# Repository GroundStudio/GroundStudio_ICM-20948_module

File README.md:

GroundStudio ICM-20948 module
====================================

Get it from [ardushop.ro](https://ardushop.ro/ro/home/2659-groundstudio-icm-20948.html)

Explore all the GroundStudio products at [GroundStudio.ro](https://groundstudio.ro/)

Description
-------------------
Low power, 9-axis MotionTracking module based on ICM-20948 chip.

Contents
-------------------

* [/Documentation](https://github.com/GroundStudio/GroundStudio_ICM-20948_module/tree/main/Documentation) -- Contains documentation written during creation of this repository, with readme.md index of its own!
* [/Firmware](https://github.com/GroundStudio/GroundStudio_ICM-20948_module/tree/main/Firmware) -- Firmware (bootloaders, etc)
* [/Hardware](https://github.com/GroundStudio/GroundStudio_ICM-20948_module/tree/main/Hardware) -- Schematics, layout.
* [/Libraries](https://github.com/GroundStudio/GroundStudio_ICM-20948_module/tree/main/Libraries) -- Arduino/CircuitPython libraries. 
* [/Tools](https://github.com/GroundStudio/GroundStudio_ICM-20948_module/tree/main) -- Tools needed for compiling, uploading bootloader, etc.

Versions
-------------------
*(Not all tags shown)*
* [V0.0.1] Initial version

License
-------------------

This is released under the [Attribution-ShareAlike 4.0 International (CC BY-SA 4.0)](https://creativecommons.org/licenses/by-sa/4.0/) license. 
**You are welcome to use this for commercial purposes.**

Please consider contributing back to this project or others to help the open-source hardware community continue to thrive and grow! 

Certifications:

[Open Source Hardware Association](https://certification.oshwa.org/ro000015.html)   
   
[
](https://certification.oshwa.org/ro000015.html)

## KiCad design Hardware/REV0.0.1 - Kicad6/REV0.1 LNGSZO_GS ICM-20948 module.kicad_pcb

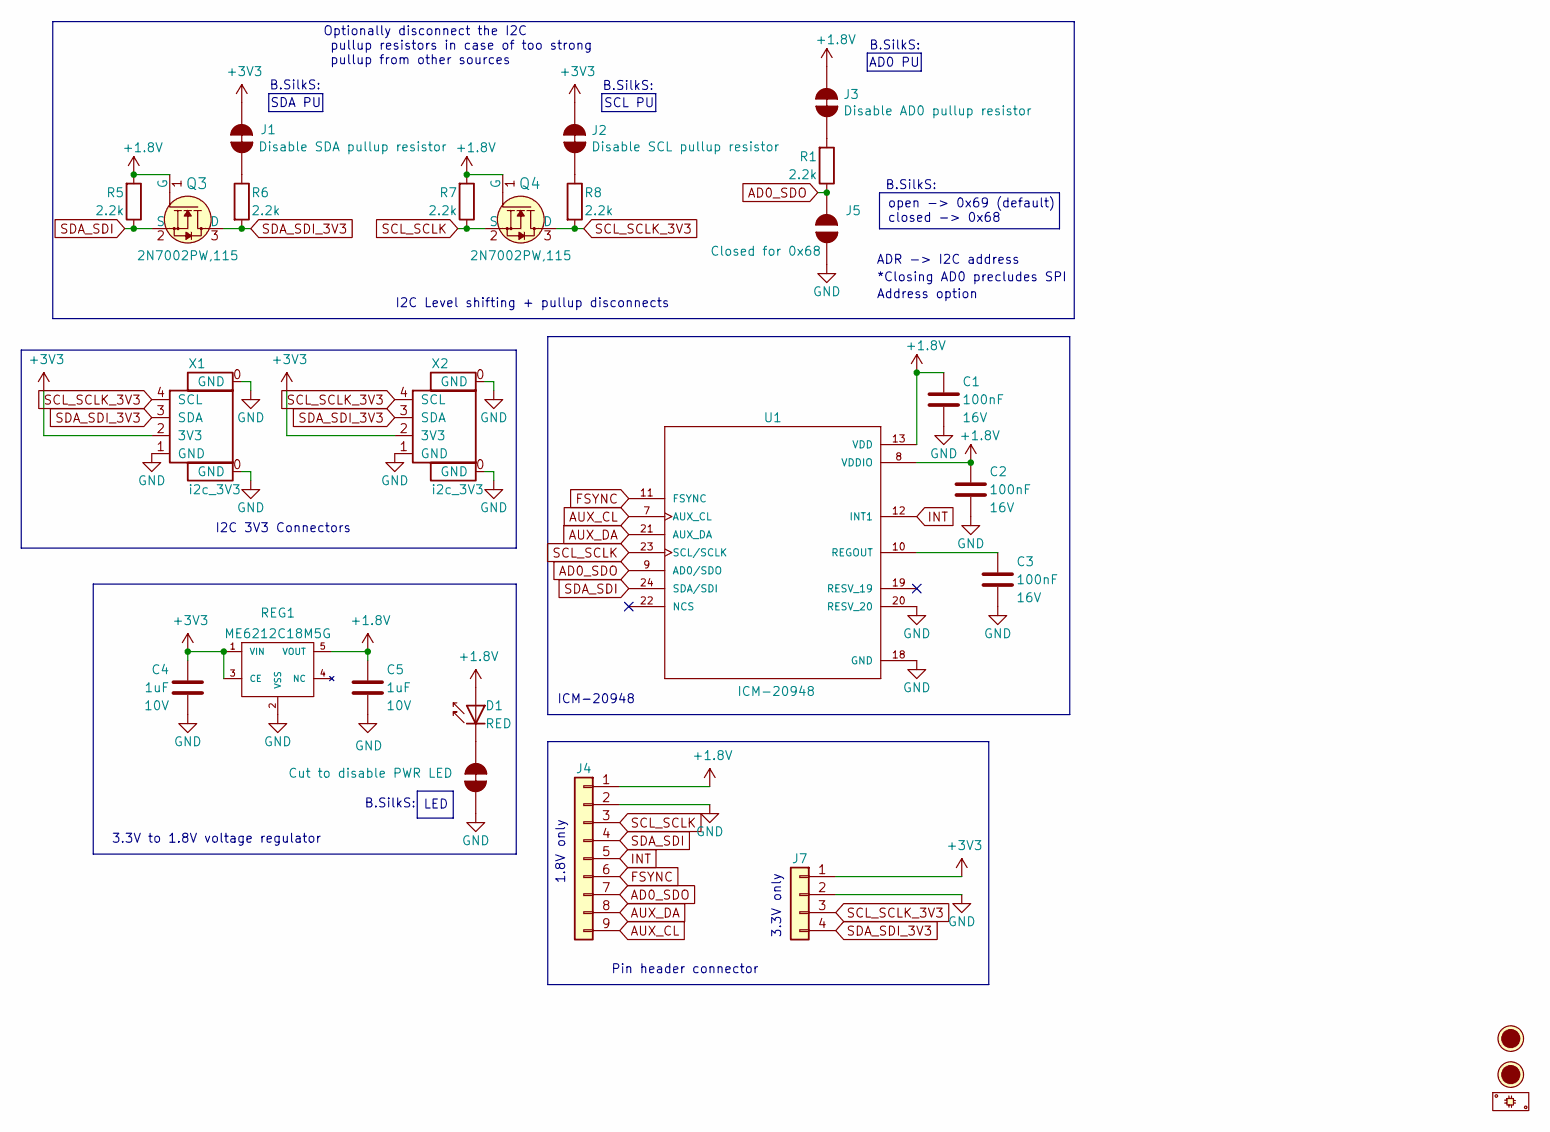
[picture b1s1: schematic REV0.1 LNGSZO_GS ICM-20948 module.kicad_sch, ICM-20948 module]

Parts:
C1, C2, C3: C_0402_100nF_16V; C_0402; Rated voltage 16V; MPN 0402B104K160CT; LCSC C83056
C4, C5: C_0402_1uF_10V; C_0402; Rated voltage 10V; MPN FS15B105K100PKG; LCSC C525324
D1: LED_0402_RED; LED_0402; MPN TZ-P2-0402RTIA1-0.45T; LCSC C779449
FID1, FID2: Fiducial; Fiducial_0.75mm_Mask1.5mm
J1: Disable SDA pullup resistor; SolderJumper_NC
J2: Disable SCL pullup resistor; SolderJumper_NC
J3: Disable AD0 pullup resistor; SolderJumper_NC
J4: PinHeader_1x09_P2.54_V_M; PinHeader_1x09_P2.54mm_Vertical_Male; MPN A2541WV-9P; LCSC C225484
J5: Closed for 0x68; SolderJumper_NO
J6: Cut to disable PWR LED; SolderJumper_NC
J7: PinHeader_1x04_P2.54_V_M; PinHeader_1x04_P2.54mm_Vertical_Male; MPN MTP125-1104S1; LCSC C358686
P1: PCB; MPN LNGSZO_GS_PCB
Q3, Q4: SOT-323 2N7002PW; SOT-323_SC-70; MPN 2N7002PW,115; LCSC C255579
R1, R5, R6, R7, R8: R_0402_2.2k; R_0402; MPN RC-02W2201FT; LCSC C258093
REG1: SOT-23-5_ME6212C18M5G; SOT-23-5; MPN ME6212C18M5G; LCSC C236669
U1: QFN-24_ICM-20948; QFN-24-0EP_3x3mm_P0.4mm_NO-EP; MPN ICM-20948; Mouser 410-ICM-20948
X1, X2: SH_1x04_P1.0_H; SH__1x04_P1.00mm_Horizontal; MPN C145956; LCSC C145956

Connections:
+1.8V: C1.1, C2.1, C5.1, D1.2 (A), J3.1, J4.1, Q3.1 (G), Q4.1 (G), R5.2, R7.2, REG1.5 (VOUT), U1.8 (VDDIO), U1.13 (VDD)
+3V3: C4.2, J1.1, J2.1, J7.1, REG1.1 (VIN), REG1.3 (CE), X1.2 (3V3), X2.2 (3V3)
AD0_SDO: J4.7, J5.1, R1.1, U1.9 (AD0/SDO)
AUX_CL: J4.9, U1.7 (AUX_CL)
AUX_DA: J4.8, U1.21 (AUX_DA)
FSYNC: J4.6, U1.11 (FSYNC)
GND: C1.2, C2.2, C3.2, C4.1, C5.2, J4.2, J5.2, J6.1, J7.2, REG1.2 (VSS), U1.18 (GND), U1.20 (RESV_20), X1.0 (GND), X1.1 (GND), X2.0 (GND), X2.1 (GND)
INT: J4.5, U1.12 (INT1)
unnamed: C3.1, U1.10 (REGOUT)
unnamed: D1.1 (K), J6.2
unnamed: J1.2, R6.1
unnamed: J2.2, R8.1
unnamed: J3.2, R1.2
SCL_SCLK: J4.3, Q4.2 (S), R7.1, U1.23 (SCL/SCLK)
SCL_SCLK_3V3: J7.3, Q4.3 (D), R8.2, X1.4 (SCL), X2.4 (SCL)
SDA_SDI: J4.4, Q3.2 (S), R5.1, U1.24 (SDA/SDI)
SDA_SDI_3V3: J7.4, Q3.3 (D), R6.2, X1.3 (SDA), X2.3 (SDA)

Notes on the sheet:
LED
I2C 3V3 Connectors
3.3V only
B.SilkS:
Address option
AD0 PU
SDA PU
SCL PU
open -> 0x69 (default) closed -> 0x68
Optionally disconnect the I2C pullup resistors in case of too strong pullup from other sources
3.3V to 1.8V voltage regulator
*Closing AD0 precludes SPI
ADR -> I2C address
ICM-20948
I2C Level shifting + pullup disconnects
Pin header connector
1.8V only

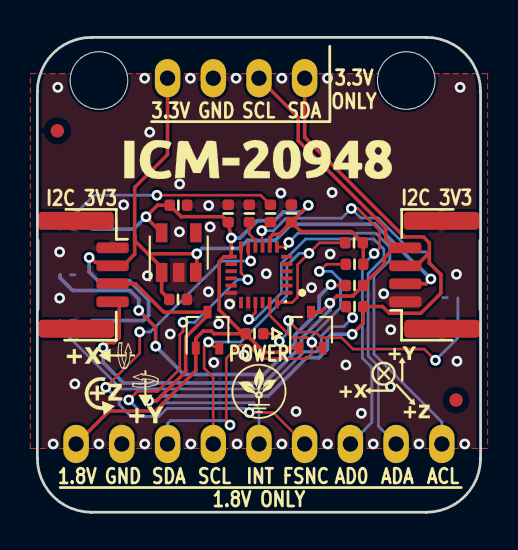
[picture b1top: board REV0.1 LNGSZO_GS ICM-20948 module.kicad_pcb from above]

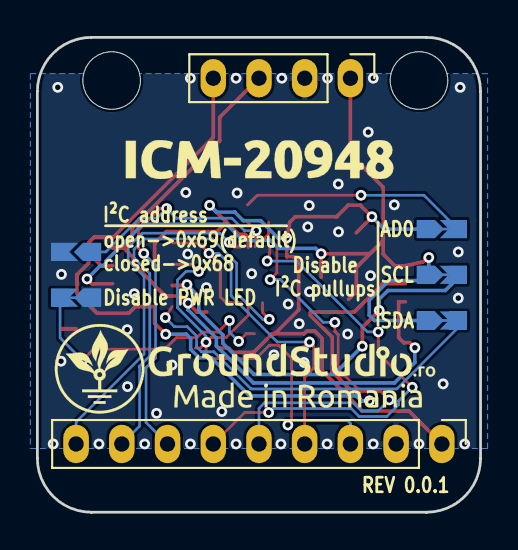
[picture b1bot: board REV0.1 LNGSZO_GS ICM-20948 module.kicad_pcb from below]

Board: 2 copper layers, 24.6 x 26.4 mm, 26 parts (7 on the bottom side), 17 nets.

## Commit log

2023-10-24 - first commit
2023-10-24 - added kicad files
2023-11-03 - added datasheet
